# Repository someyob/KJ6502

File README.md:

# KJ6502
Inspired by the Ben Eater video series.

Note:  the expension header has 2 errors, Pins 15 through 21 should be
A12, A13, A14 and A15 respectively.  These are not intended to be used anyway.

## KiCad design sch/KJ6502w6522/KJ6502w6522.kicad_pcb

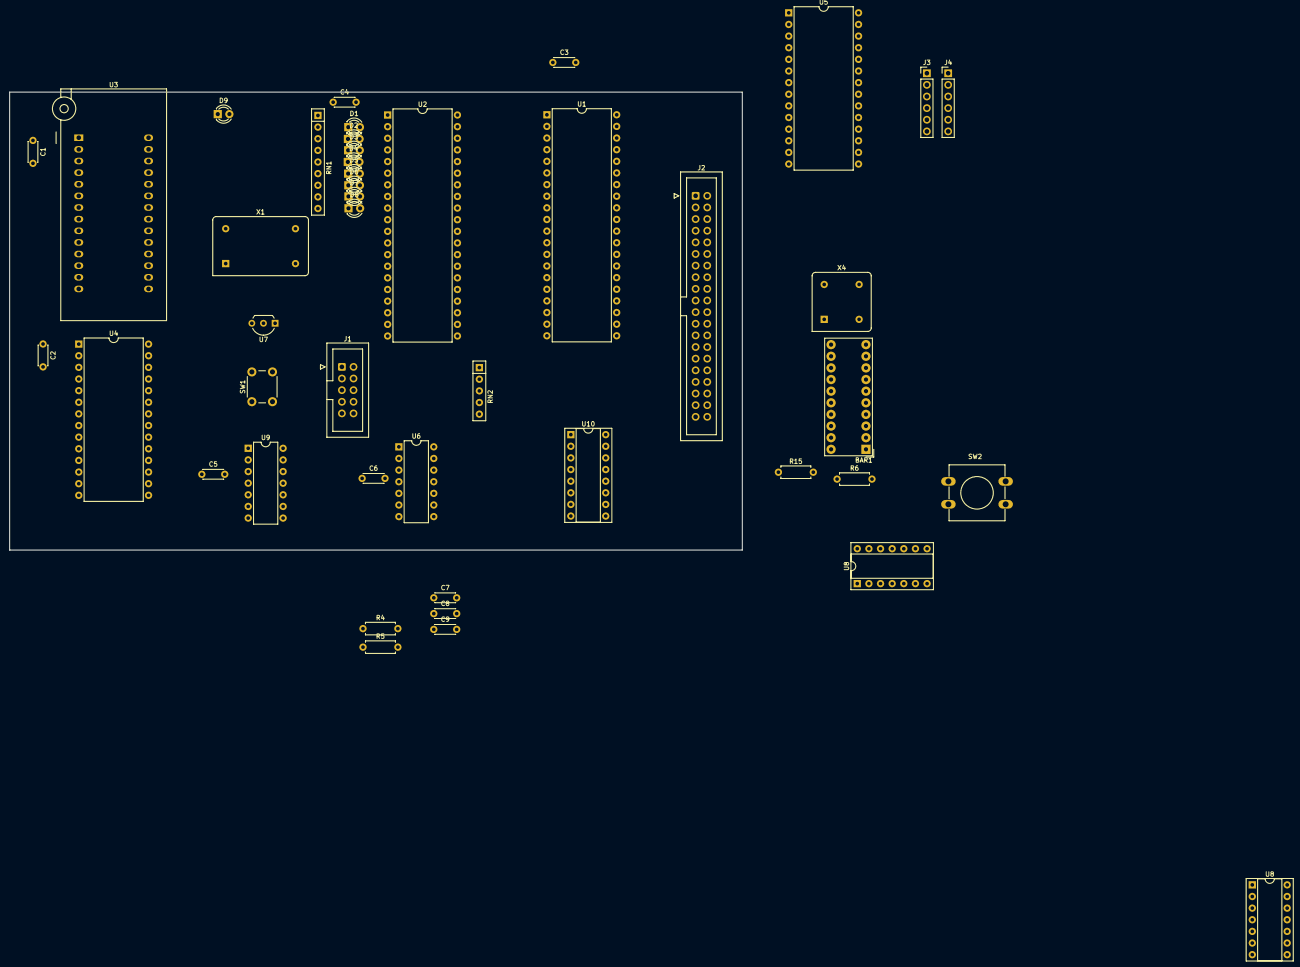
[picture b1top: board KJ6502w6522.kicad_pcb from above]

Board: 2 copper layers, 160.0 x 100.0 mm, 44 parts (0 on the bottom side), 75 nets, no tracks yet.

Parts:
BAR1: HDSP-4830_2; HDSP-4830
C1, C2, C3, C4, C5, C6, C7, C8, C9: 100nF; C_Disc_D4.3mm_W1.9mm_P5.00mm
D1, D2, D3, D4, D5, D6, D7, D8, D9: LED; LED_D3.0mm
J1: Keypad / GP I/O; IDC-Header_2x05_P2.54mm_Vertical
J2: Conn_02x20_Odd_Even; IDC-Header_2x20_P2.54mm_Vertical
J3: Serial; PinHeader_1x06_P2.54mm_Vertical
J4: CACB; PinHeader_1x06_P2.54mm_Vertical
R4, R5: 10K; R_Axial_DIN0207_L6.3mm_D2.5mm_P7.62mm_Horizontal
R6: 220; R_Axial_DIN0207_L6.3mm_D2.5mm_P7.62mm_Horizontal
R15: 1K; R_Axial_DIN0207_L6.3mm_D2.5mm_P7.62mm_Horizontal
RN1: 220; R_Array_SIP9
RN2: 3k3; R_Array_SIP5
SW1: Reset; SW_PUSH_6mm
SW2: NMI; SW_PUSH-12mm
U1: W65C02SxP; DIP-40_W15.24mm
U2: W65C22NxP; DIP-40_W15.24mm
U3: 28C256; DIP_Socket-28_W11.9_W12.7_W15.24_W17.78_W18.5_3M_228-1277-0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
U4: CY62256-70PC; DIP-28_W15.24mm
U5: W65C51NxP; DIP-28_W15.24mm
U6: 74HC21; DIP-14_W7.62mm
U7: TO-92L_Inline_Wide
U8, U8#2: 74HC14; DIP-14_W7.62mm_Socket
U9: 74HC00; DIP-14_W7.62mm
U10: 74HC138; DIP-16_W7.62mm_Socket
X1: 1MHz; Oscillator_DIP-14
X4: TFT660; Oscillator_DIP-8

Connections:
/A0: U1.9 (A0), U2.38 (RS0), U3.10 (A0), U4.10 (A0), U5.13 (RS0)
/A1: U1.10 (A1), U2.37 (RS1), U3.9 (A1), U4.9 (A1), U5.14 (RS1)
/A2: U1.11 (A2), U2.36 (RS2), U3.8 (A2), U4.8 (A2)
/A3: U1.12 (A3), U2.35 (RS3), U3.7 (A3), U4.7 (A3)
/A4: U1.13 (A4), U3.6 (A4), U4.6 (A4)
/A5: U1.14 (A5), U3.5 (A5), U4.5 (A5)
/A6: U1.15 (A6), U3.4 (A6), U4.4 (A6)
/A7: U1.16 (A7), U3.3 (A7), U4.3 (A7)
/A11: U1.20 (A11), U3.23 (A11), U4.23 (A11)
/A15: U1.25 (A15), U9.9, U9.10
/D0: U1.33 (D0), U2.33 (D0), U3.11 (D0), U4.11 (Q0), U5.18 (D0)
/D1: U1.32 (D1), U2.32 (D1), U3.12 (D1), U4.12 (Q1), U5.19 (D1)
/D2: U1.31 (D2), U2.31 (D2), U3.13 (D2), U4.13 (Q2), U5.20 (D2)
/D3: U1.30 (D3), U2.30 (D3), U3.15 (D3), U4.15 (Q3), U5.21 (D3)
/D4: U1.29 (D4), U2.29 (D4), U3.16 (D4), U4.16 (Q4), U5.22 (D4)
/D5: U1.28 (D5), U2.28 (D5), U3.17 (D5), U4.17 (Q5), U5.23 (D5)
/D6: U1.27 (D6), U2.27 (D6), U3.18 (D6), U4.18 (Q6), U5.24 (D6)
/D7: U1.26 (D7), U2.26 (D7), U3.19 (D7), U4.19 (Q7), U5.25 (D7)
A8: U1.17 (A8), U3.25 (A8), U4.25 (A8), U10.1 (A0)
A9: U1.18 (A9), U3.24 (A9), U4.24 (A9), U10.2 (A1)
A10: U1.19 (A10), U3.21 (A10), U4.21 (A10), U10.3 (A2)
A12: U1.22 (A12), U3.2 (A12), U4.2 (A12), U6.10
A13: U1.23 (A13), U3.26 (A13), U4.26 (A13), U6.12
A14: U1.24 (A14), U3.1 (A14), U4.1 (A14), U6.13
CA1: J4.1, U2.40 (CA1)
CA2: J4.2, U2.39 (CA2)
CB1: J4.3, U2.18 (CB1)
CB2: J4.4, U2.19 (CB2)
CLK: U1.37 (ϕ0), U2.25 (ϕ2), U5.27 (ϕ2), U9.13, X1.8 (OUT)
GND: C1.2, C2.2, C3.2, C4.2, C5.2, C6.2, C7.2, C8.2, C9.2, D9.1 (K), J1.1, J3.2, J4.6, RN1.1 (common), SW1.1, SW2.1, U1.21 (VSS), U2.1 (VSS), U3.14 (GND), U3.22 (~OE), U4.14 (GND), U5.1 (VSS), U5.9 (~CTS), U5.16 (~DCD), U5.17 (~DSR), U6.7 (GND), U7.3 (GND), U9.7 (GND), U10.4 (E1), U10.5 (E2), U10.8 (GND), X1.7 (GND), X4.4 (GND)
IRQ1: RN2.4 (R3), U2.21 (~IRQ), U6.4
IRQ2: RN2.5 (R4), U5.26 (~IRQ), U6.5
IRQ3: RN2.2 (R1), U6.1
IRQ4: RN2.3 (R2), U6.2
I/O: U2.24 (CS1), U4.22 (~OE), U5.2 (CS1), U6.8
I/O 1: U2.23 (~CS2), U10.15 (O0)
I/O 2: U5.3 (~CS2), U10.14 (O1)
LED1: BAR1.3 (A), D1.2 (A), U2.2 (PA0)
LED2: BAR1.4 (A), D2.2 (A), U2.3 (PA1)
LED3: BAR1.5 (A), D3.2 (A), U2.4 (PA2)
LED4: BAR1.6 (A), D4.2 (A), U2.5 (PA3)
LED5: BAR1.7 (A), D5.2 (A), U2.6 (PA4)
LED6: BAR1.8 (A), D6.2 (A), U2.7 (PA5)
LED7: BAR1.9 (A), D7.2 (A), U2.8 (PA6)
LED8: BAR1.10 (A), D8.2 (A), U2.9 (PA7)
NMI: U1.6 (~NMI), U8#2.12
unnamed: C9.1, R5.1, U8#2.13
unnamed: D1.1 (K), RN1.2 (R1)
unnamed: D2.1 (K), RN1.3 (R2)
unnamed: D3.1 (K), RN1.4 (R3)
unnamed: D4.1 (K), RN1.5 (R4)
unnamed: D5.1 (K), RN1.6 (R5)
unnamed: D6.1 (K), RN1.7 (R6)
unnamed: D7.1 (K), RN1.8 (R7)
unnamed: D8.1 (K), RN1.9 (R8)
unnamed: D9.2 (A), R6.2
unnamed: J3.3, U5.12 (RxD)
unnamed: J3.4, U5.10 (TxD)
unnamed: R4.2, R5.2, SW2.2
unnamed: R15.2, U1.2 (RDY)
unnamed: U1.4 (~IRQ), U6.6
unnamed: U5.6 (XTAL1), X4.5 (OUT)
PB0: J1.2, U2.10 (PB0)
PB1: J1.3, U2.11 (PB1)
PB2: J1.4, U2.12 (PB2)
PB3: J1.5, U2.13 (PB3)
PB4: J1.6, U2.14 (PB4)
PB5: J1.7, U2.15 (PB5)
PB6: J1.8, U2.16 (PB6)
PB7: J1.9, U2.17 (PB7)
RAMSEL: U4.20 (~CS), U9.11
ROMSEL: U3.20 (~CS), U6.9, U9.8, U9.12
RST: SW1.2, U1.40 (~RES), U2.34 (~RES), U5.4 (~RES), U7.1 (RST)
R/W: U1.34 (R/~W), U2.22 (R/~W), U4.27 (~WE), U5.28 (R/~W)
VCC: BAR1.1 (A), C1.1, C2.1, C3.1, C4.1, C5.1, C6.1, C7.1, C8.1, R4.1, R6.1, R15.1, RN2.1 (common), U1.8 (VDD), U1.36 (BE), U2.20 (VCC), U3.27 (~WE), U3.28 (VCC), U4.28 (VCC), U5.15 (VCC), U6.14 (VCC), U7.2 (VCC), U9.14 (VCC), U10.6 (E3), U10.16 (VCC), X1.14 (Vcc), X4.8 (Vcc)
